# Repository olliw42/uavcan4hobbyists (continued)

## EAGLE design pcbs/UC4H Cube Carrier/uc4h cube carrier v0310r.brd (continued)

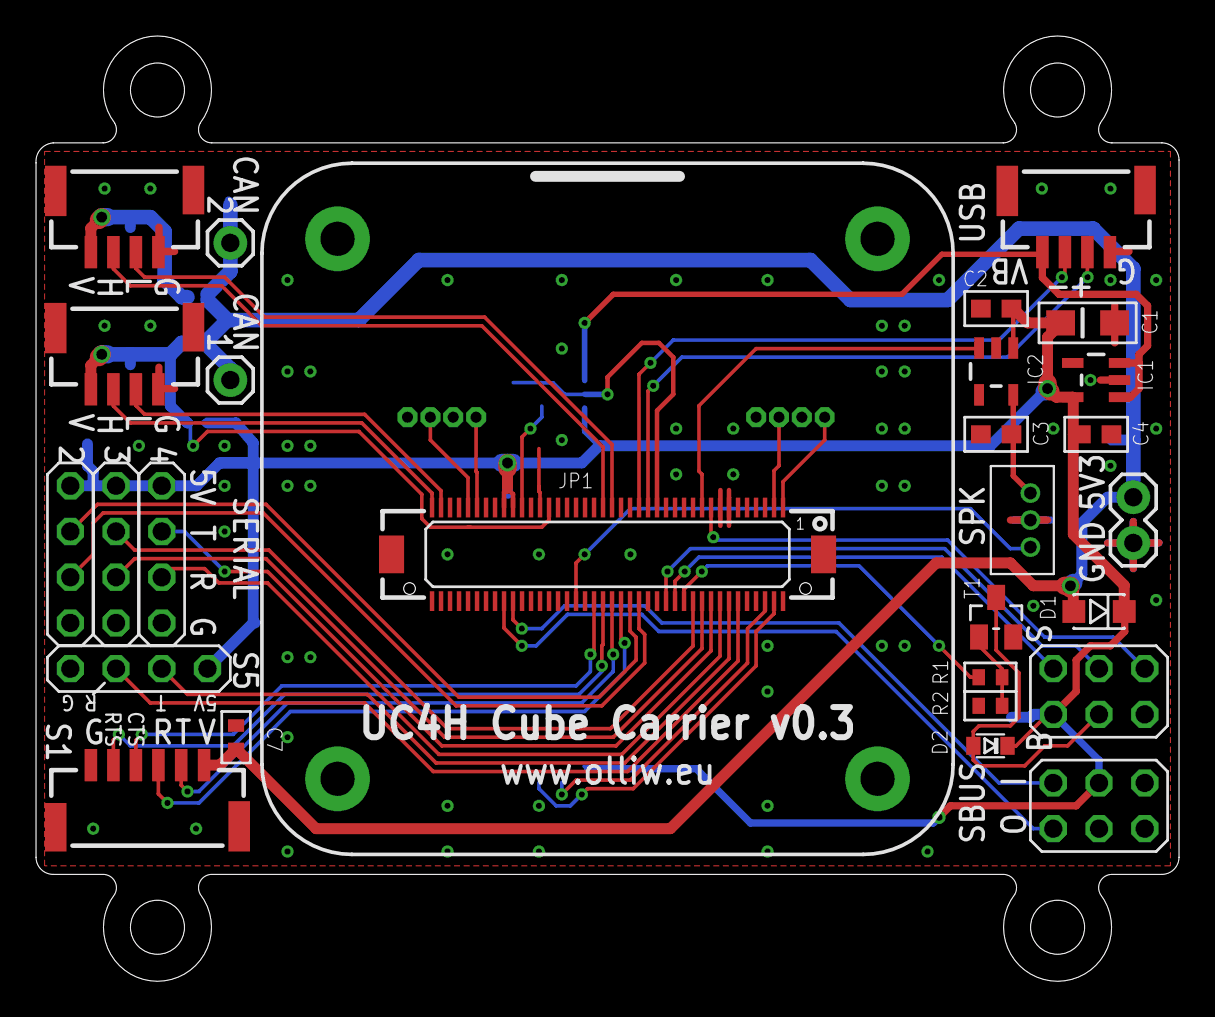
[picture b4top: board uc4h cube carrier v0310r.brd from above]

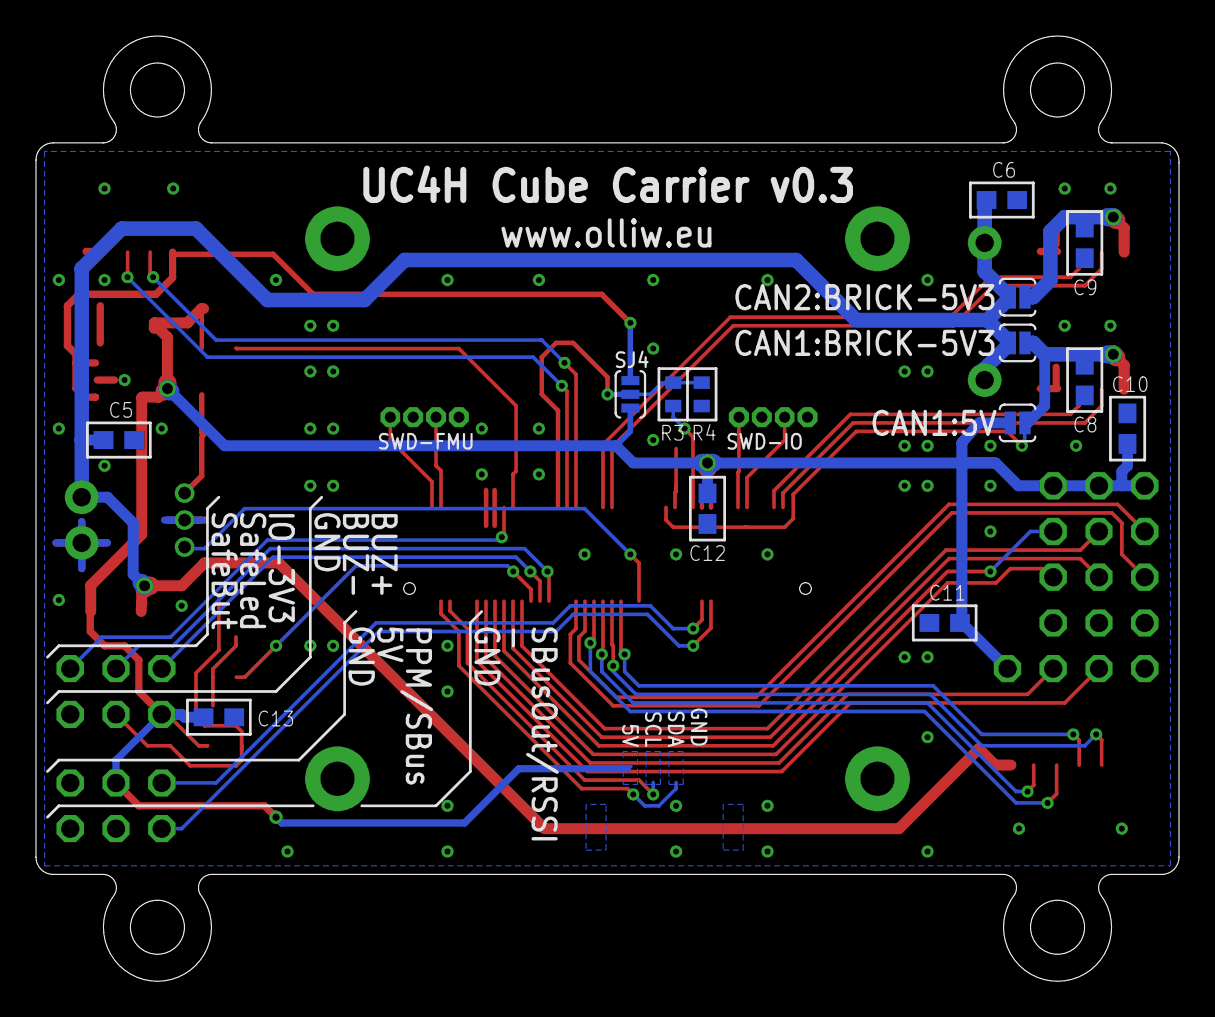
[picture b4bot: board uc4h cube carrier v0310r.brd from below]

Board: 2 copper layers, 63.5 x 52.5 mm, 46 parts (15 on the bottom side), 44 nets.

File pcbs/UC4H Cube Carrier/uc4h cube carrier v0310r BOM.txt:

Stückliste exportiert aus C:/Users/Olli/Documents/GitHub/uavcan4hobbyists/pcbs/UC4H Cube Carrier/uc4h cube carrier v0310r.sch am 06.04.2019 08:51

Part Value                Device                 Package                           Description                          BOM
C1   10u/10V              CPOL-EUSMCA            SMC_A                             POLARIZED CAPACITOR, European symbol    
C2   100n                 C-EUC0603              C0603                             CAPACITOR, European symbol              
C3   100n                 C-EUC0603              C0603                             CAPACITOR, European symbol              
C4   1u                   C-EUC0603              C0603                             CAPACITOR, European symbol              
C5   100n                 C-EUC0603              C0603                             CAPACITOR, European symbol              
C6   100n                 C-EUC0603              C0603                             CAPACITOR, European symbol              
C7   100n                 C-EUC0402              C0402                             CAPACITOR, European symbol              
C8   100n                 C-EUC0603              C0603                             CAPACITOR, European symbol              
C9   100n                 C-EUC0603              C0603                             CAPACITOR, European symbol              
C10  100n                 C-EUC0603              C0603                             CAPACITOR, European symbol              
C11  100n                 C-EUC0603              C0603                             CAPACITOR, European symbol              
C12  100n                 C-EUC0603              C0603                             CAPACITOR, European symbol              
C13  100n                 C-EUC0603              C0603                             CAPACITOR, European symbol              
D1   PMEG3010ER           DIODE-SCHOTTKYSOD123-W SOD123W-DIODE                                                             
D2   BAT54J               DIODE-SOD110-R         SOD110-R                          DIODE                                   
IC1  MAX40200             V_REG_TPS76433SOT23-5  SOT23-5                           Voltage Regulator                       
IC2  TC1185-3.3VCT713     V_REG_TPS76433SOT23-5  SOT23-5                           Voltage Regulator                       
JP1  DF17(1.0H)-80DP-0.5V PIX-CUBE-VIA           PIX-CUBE-DF17(1.0H)-80DP-0.5V-VIA                                         
JP2  USB                  JST-GH-4TOP-ENTRY      BM04B-GHS-TBT                                                             
JP3  SPK                  B3B-ZR                 B3B-ZR                            JST-ZH Connector                        
JP4  CAN1                 JST-GH-4TOP-ENTRY      BM04B-GHS-TBT                                                             
JP5  CAN2                 JST-GH-4TOP-ENTRY      BM04B-GHS-TBT                                                             
JP6  SERIAL1              JST-GH-6TOP-ENTRY      BM06B-GHS-TBT                                                             
JP7  SERIAL2              PINHEAD_4X1            PINHEAD_4X1                                                               
JP8  SERIAL3              PINHEAD_4X1            PINHEAD_4X1                                                               
JP9  SERIAL4              PINHEAD_4X1            PINHEAD_4X1                                                               
JP10 SERIAL5              PINHEAD_4X1            PINHEAD_4X1                                                               
PH1  VDD-BRICK            M02PTH                 1X02                              Header 2                                
PH2  SBUS                 PINHEAD_3X2            PINHEAD_3X2                                                               
PH3  SAFEBUZ              PINHEAD_3X2            PINHEAD_3X2                                                               
PH4  CAN-HIPWR1           M01PTH                 1X01                              Header 1                                
PH5  CAN-HIPWR2           M01PTH                 1X01                              Header 1                                
PH6  SWD                  P4X1_1P27-OCT_BILEX    4X1_1P27_OCT_BILEX                                                        
PH7  SWD2                 P4X1_1P27-OCT_BILEX    4X1_1P27_OCT_BILEX                                                        
R1   10k                  R-EU_R0402             R0402                             RESISTOR, European symbol               
R2   10k                  R-EU_R0402             R0402                             RESISTOR, European symbol               
R3   10k                  R-EU_R0402             R0402                             RESISTOR, European symbol               
R4   470                  R-EU_R0402             R0402                             RESISTOR, European symbol               
SH1  SHORT-HT5            SHORT-HT5              SHORT_TOP-50                      Short between two nets               no 
SH2  SHORT-HT5            SHORT-HT5              SHORT_TOP-50                      Short between two nets               no 
SH3  SHORT-HT5            SHORT-HT5              SHORT_TOP-50                      Short between two nets               no 
SJ1  PWR                  SJ-2WAY-WPASTECONNECT  SJ-2WAY-BIG-WPASTEC                                                       
SJ2  PWR                  SJ-2WAY-STANDARD       SJ-2WAY-BIG                                                               
SJ3  PWR                  SJ-2WAY-WPASTECONNECT  SJ-2WAY-BIG-WPASTEC                                                       
SJ4  SJ-3WAY-03           SJ-3WAY-03             SJ-3WAY-WPASTEC                                                           
T1   FET-NSOT23           FET-NSOT23             SOT23

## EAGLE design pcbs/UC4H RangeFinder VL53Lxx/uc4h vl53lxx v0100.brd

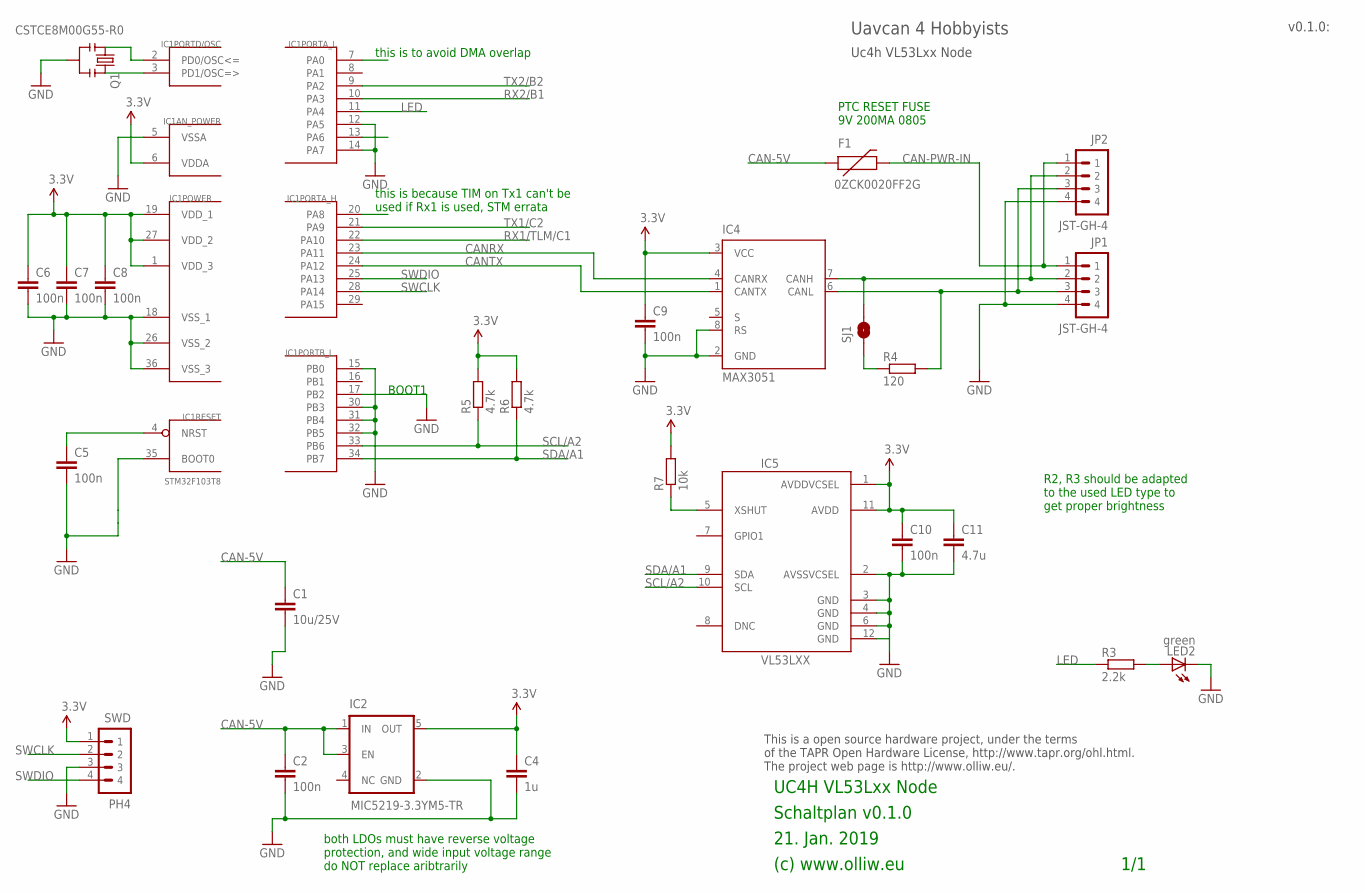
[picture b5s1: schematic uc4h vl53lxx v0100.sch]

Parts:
C1: 10u/25V; C1206
C2: 100n; C0603K
C4: 1u; C0603K
C5, C6, C7, C8, C9, C10: 100n; C0402
C11: 4.7u; C0603K
F1: 0ZCK0020FF2G; FUSE-0805
IC1: STM32F103T8; VFQFPN36
IC2: MIC5219-3.3YM5-TR; SOT23-5
IC4: MAX3051; SOT23-8
IC5: VL53LXX
JP1, JP2: JST-GH-4; SM04B-GHS-TB
LED2: green; CHIPLED_0603
Q1: CSTCE8M00G55-R0; RESONATOR-SMD
R3: 2.2k; R0402
R4: 120; R0402
R5, R6: 4.7k; R0402
R7: 10k; R0402
SJ1: SOLDERJUMPERNO; SJ_2S-NO
SWD: PH4; 4X1_1P27_OCT_BILEX

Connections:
3.3V: C4.1, C6.1, C7.1, C8.1, C9.1, C10.1, C11.1, IC1.1 (VDD_3), IC1.6 (VDDA), IC1.19 (VDD_1), IC1.27 (VDD_2), IC2.5 (OUT), IC4.3 (VCC), IC5.1 (AVDDVCSEL), IC5.11 (AVDD), R5.2, R6.2, R7.2, SWD.1
CAN-5V: C1.1, C2.1, F1.1, IC2.1 (IN), IC2.3 (EN)
CAN-PWR-IN: F1.2, JP1.1, JP2.1
CANH: IC4.7 (CANH), JP1.2, JP2.2, SJ1.2
CANL: IC4.6 (CANL), JP1.3, JP2.3, R4.2
CANRX: IC1.23 (PA11), IC4.4 (CANRX)
CANTX: IC1.24 (PA12), IC4.1 (CANTX)
GND: C1.2, C2.2, C4.2, C5.2, C6.2, C7.2, C8.2, C9.2, C10.2, C11.2, IC1.5 (VSSA), IC1.12 (PA5), IC1.14 (PA7), IC1.15 (PB0), IC1.17 (PB2), IC1.18 (VSS_1), IC1.26 (VSS_2), IC1.30 (PB3), IC1.31 (PB4), IC1.32 (PB5), IC1.35 (BOOT0), IC1.36 (VSS_3), IC2.2 (GND), IC4.2 (GND), IC4.8 (RS), IC5.2 (AVSSVCSEL), IC5.3 (GND), IC5.4 (GND), IC5.6 (GND), IC5.12 (GND), JP1.4, JP2.4, LED2.C, Q1.2, SWD.3
LED: IC1.11 (PA4), R3.1
unnamed: C5.1, IC1.4 (NRST)
unnamed: LED2.A, R3.2
unnamed: R4.1, SJ1.1
unnamed: IC1.2 (PD0/OSC<=), Q1.1
unnamed: IC1.3 (PD1/OSC=>), Q1.3
unnamed: IC5.5 (XSHUT), R7.1
RX1/TLM/C1: IC1.22 (PA10)
RX2/B1: IC1.10 (PA3)
SCL/A2: IC1.33 (PB6), IC5.10 (SCL), R5.1
SDA/A1: IC1.34 (PB7), IC5.9 (SDA), R6.1
SWCLK: IC1.28 (PA14), SWD.2
SWDIO: IC1.25 (PA13), SWD.4
TX1/C2: IC1.21 (PA9)
TX2/B2: IC1.9 (PA2)

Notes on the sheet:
21. Jan. 2019
(c) www.olliw.eu
UC4H VL53Lxx Node
Schaltplan v0.1.0
This is a open source hardware project, under the terms of the TAPR Open Hardware License, http://www.tapr.org/ohl.html. The project web page is http://www.olliw.eu/.
1/1
Uc4h VL53Lxx Node
Uavcan 4 Hobbyists
BOOT1
PTC RESET FUSE 9V 200MA 0805
both LDOs must have reverse voltage protection, and wide input voltage range do NOT replace aribtrarily
this is to avoid DMA overlap
this is because TIM on Tx1 can't be used if Rx1 is used, STM errata
v0.1.0:
R2, R3 should be adapted to the used LED type to get proper brightness

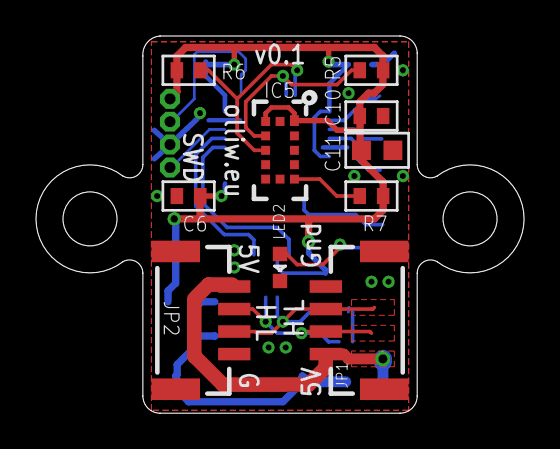
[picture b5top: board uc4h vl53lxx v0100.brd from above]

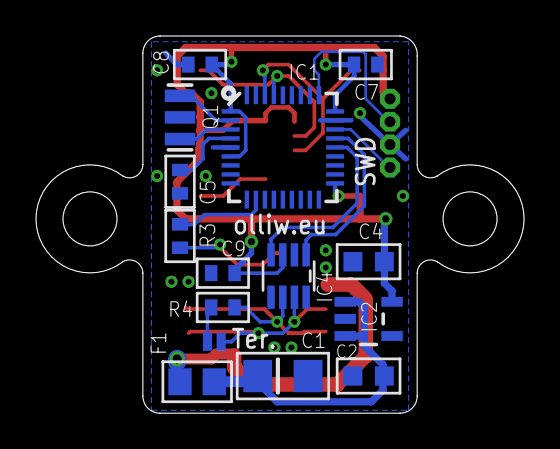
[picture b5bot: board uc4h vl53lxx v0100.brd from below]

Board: 2 copper layers, 27.1 x 21.0 mm, 26 parts (15 on the bottom side), 19 nets.

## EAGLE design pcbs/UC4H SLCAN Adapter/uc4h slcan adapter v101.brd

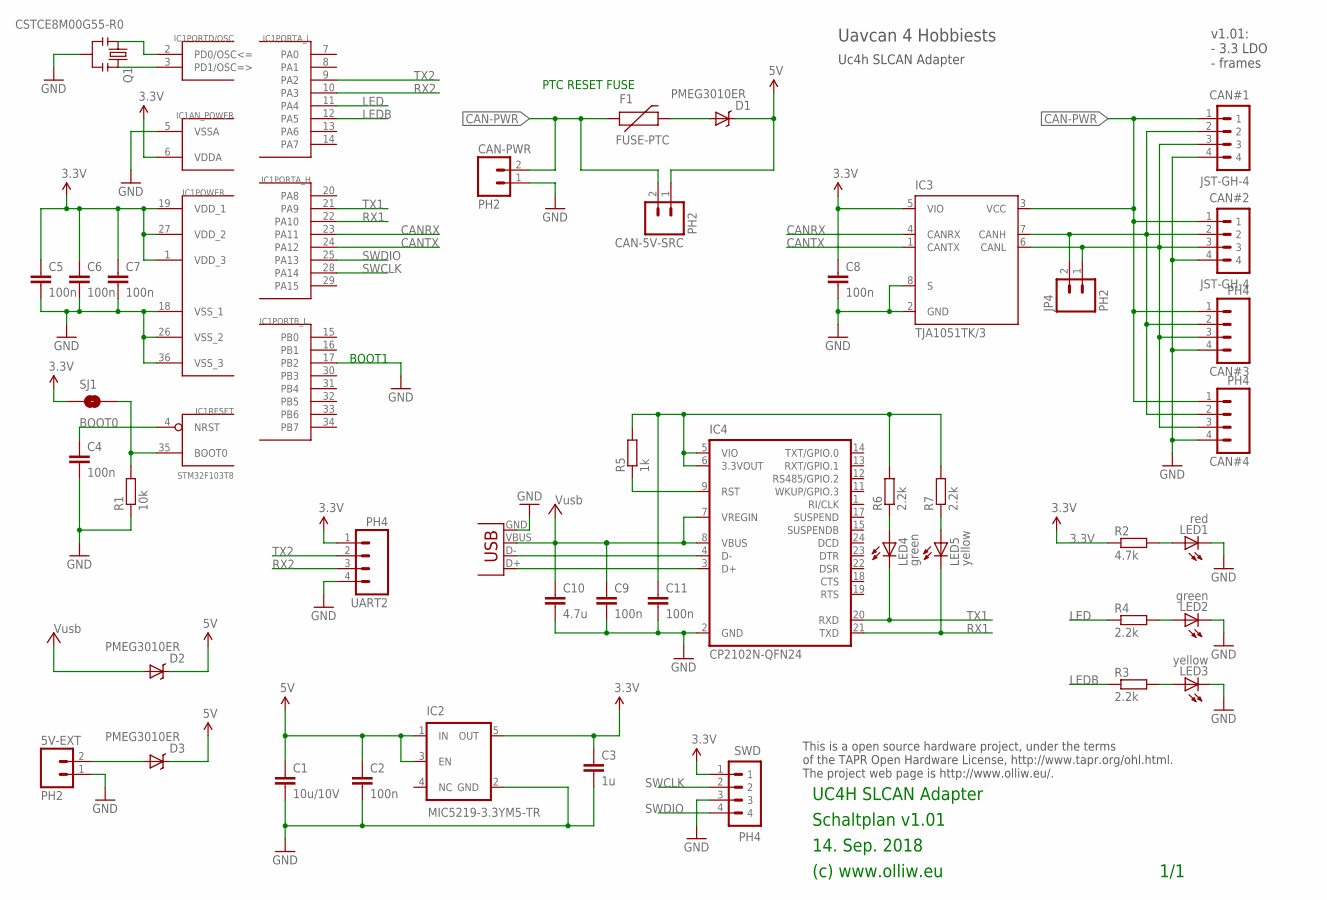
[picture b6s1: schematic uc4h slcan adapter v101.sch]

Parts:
5V-EXT: PH2; 1X02
C1: 10u/10V; C1206
C2, C4, C5, C6, C7, C8, C9, C11: 100n; C0603K
C3: 1u; C0603K
C10: 4.7u; C0805
CAN#1, CAN#2: JST-GH-4; SM04B-GHS-TB
CAN#3, CAN#4: PH4; 1X04
CAN-5V-SRC: PH2; 1X02
CAN-PWR: PH2; 1X02
D1, D2, D3: PMEG3010ER; SOD123W-DIODE
F1: FUSE-PTC; FUSE-1206
IC1: STM32F103T8; VFQFPN36
IC2: MIC5219-3.3YM5-TR; SOT23-5
IC3: TJA1051TK/3; HVSON8
IC4: CP2102N-QFN24; QFN24-CP2102N
JP4: PH2; 1X02
LED1: red; CHIPLED_0603
LED2, LED4: green; CHIPLED_0603
LED3, LED5: yellow; CHIPLED_0603
Q1: CSTCE8M00G55-R0; RESONATOR-SMD
R1: 10k; R0603
R2: 4.7k; R0603
R3, R4, R6, R7: 2.2k; R0603
R5: 1k; R0603
SJ1: BOOT0; SJ_2S-NO
SWD: PH4; 4X1_1P27_OCT_BILEX
UART2: PH4; 1X04
USB: Amphenol 10118192-0001LF; USB-MICROB

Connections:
3.3V: C3.1, C5.1, C6.1, C7.1, C8.1, IC1.1 (VDD_3), IC1.6 (VDDA), IC1.19 (VDD_1), IC1.27 (VDD_2), IC2.5 (OUT), IC3.5 (VIO), R2.1, SJ1.1, SWD.1, UART2.1
3.3V-CP2102: C11.1, IC4.5 (VIO), IC4.6 (3.3VOUT), R5.2, R6.2, R7.2
5V: C1.1, C2.1, CAN-5V-SRC.1, D1.C, D2.C, D3.C, IC2.1 (IN), IC2.3 (EN)
5V-CAN-FUSE: D1.A, F1.4 (2)
CAN-PWR: CAN#1.1, CAN#2.1, CAN#3.1, CAN#4.1, CAN-5V-SRC.2, CAN-PWR.2, F1.3 (1), IC3.3 (VCC)
CANH: CAN#1.2, CAN#2.2, CAN#3.2, CAN#4.2, IC3.7 (CANH), JP4.2
CANL: CAN#1.3, CAN#2.3, CAN#3.3, CAN#4.3, IC3.6 (CANL), JP4.1
CANRX: IC1.23 (PA11), IC3.4 (CANRX)
CANTX: IC1.24 (PA12), IC3.1 (CANTX)
GND: 5V-EXT.1, C1.2, C2.2, C3.2, C4.2, C5.2, C6.2, C7.2, C8.2, C9.2, C10.2, C11.2, CAN#1.4, CAN#2.4, CAN#3.4, CAN#4.4, CAN-PWR.1, IC1.5 (VSSA), IC1.17 (PB2), IC1.18 (VSS_1), IC1.26 (VSS_2), IC1.36 (VSS_3), IC2.2 (GND), IC3.2 (GND), IC3.8 (S), IC4.2 (GND), LED1.C, LED2.C, LED3.C, Q1.2, R1.1, SWD.3, UART2.4, USB.GND
LED: IC1.11 (PA4), R4.1
LEDB: IC1.12 (PA5), R3.1
unnamed: C4.1, IC1.4 (NRST)
unnamed: LED3.A, R3.2
unnamed: IC1.35 (BOOT0), R1.2, SJ1.2
unnamed: IC1.2 (PD0/OSC<=), Q1.1
unnamed: IC1.3 (PD1/OSC=>), Q1.3
unnamed: LED2.A, R4.2
unnamed: LED1.A, R2.2
unnamed: 5V-EXT.2, D3.A
unnamed: IC4.9 (RST), R5.1
unnamed: LED4.A, R6.1
unnamed: IC4.4 (D-), USB.D-
unnamed: LED5.A, R7.1
unnamed: IC4.3 (D+), USB.D+
RX1: IC1.22 (PA10), IC4.21 (TXD), LED5.C
RX2: IC1.10 (PA3), UART2.3
SWCLK: IC1.28 (PA14), SWD.2
SWDIO: IC1.25 (PA13), SWD.4
TX1: IC1.21 (PA9), IC4.20 (RXD), LED4.C
TX2: IC1.9 (PA2), UART2.2
VUSB: C9.1, C10.1, D2.A, IC4.7 (VREGIN), IC4.8 (VBUS), USB.VBUS

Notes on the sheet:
14. Sep. 2018
(c) www.olliw.eu
UC4H SLCAN Adapter
Schaltplan v1.01
This is a open source hardware project, under the terms of the TAPR Open Hardware License, http://www.tapr.org/ohl.html. The project web page is http://www.olliw.eu/.
1/1
Uc4h SLCAN Adapter
Uavcan 4 Hobbiests
BOOT1
v1.01: - 3.3 LDO - frames
PTC RESET FUSE

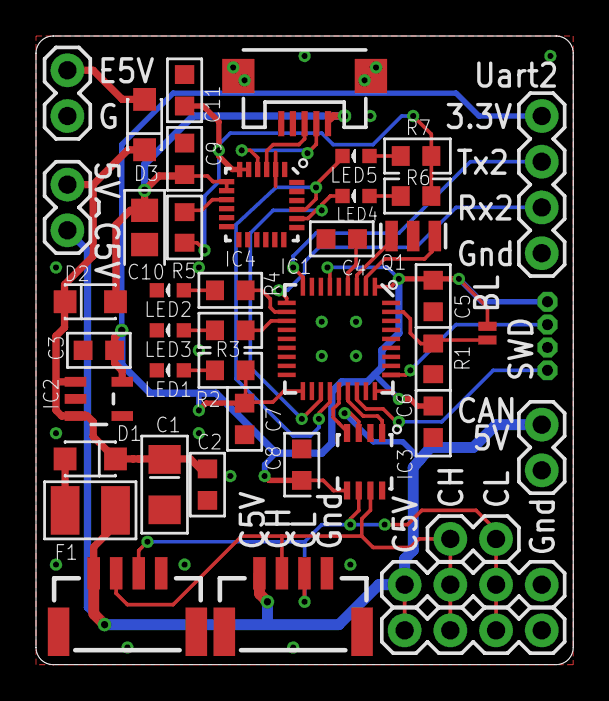
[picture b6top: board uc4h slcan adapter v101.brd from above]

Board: 2 copper layers, 29.8 x 34.9 mm, 44 parts (0 on the bottom side), 32 nets.

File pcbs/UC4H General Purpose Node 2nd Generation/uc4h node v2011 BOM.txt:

Stückliste exportiert aus C:/Users/Olli/Documents/Elektronik/Eagle/Uavcan4Hobby/uc4h node v2010.sch am 02.08.2018 07:51

Part Value             Device                Package            Description                  
C1   10u/25V           C-EUC1206             C1206              CAPACITOR, European symbol   
C2   100n              C-EUC0603K            C0603K             CAPACITOR, European symbol   
C3   1u                C-EUC0603K            C0603K             CAPACITOR, European symbol   
C4   1u                C-EUC0603K            C0603K             CAPACITOR, European symbol   
C5   100n              C-EUC0603K            C0603K             CAPACITOR, European symbol   
C6   100n              C-EUC0603K            C0603K             CAPACITOR, European symbol   
C7   100n              C-EUC0603K            C0603K             CAPACITOR, European symbol   
C8   100n              C-EUC0603K            C0603K             CAPACITOR, European symbol   
C9   100n              C-EUC0603K            C0603K             CAPACITOR, European symbol   
F1   0ZCK0020FF2G      FUSE-PTCFUSE-0805     FUSE-0805                                       
IC1  STM32F103T8       STM32F10XTXU6         VFQFPN36           STM32F101/103 36pad VFQPFN36 
IC2  MIC5219-5.0YM5-TR V_REG_TPS76433SOT23-5 SOT23-5            Voltage Regulator            
IC3  MIC5219-3.3YM5-TR V_REG_TPS76433SOT23-5 SOT23-5            Voltage Regulator            
IC4  TJA1051TK/3       TJA1051TK/3           HVSON8                                          
JP1  JST-GH-4          JST-GH-4              SM04B-GHS-TB                                    
JP2  JST-GH-4          JST-GH-4              SM04B-GHS-TB                                    
JP3                    M04PTH                1X04               Header 4                     
JP5                    M02PTH                1X02               Header 2                     
JP6  M01PTH            M01PTH                1X01               Header 1                     
LED1 red               LEDCHIPLED_0603       CHIPLED_0603       LED                          
LED2 green             LEDCHIPLED_0603       CHIPLED_0603       LED                          
Q1   CSTCE8M00G55-R0   RESONATORSMD          RESONATOR-SMD      Resonator                    
R1   10k               R-EU_R0603            R0603              RESISTOR, European symbol    
R2   4.7k              R-EU_R0603            R0603              RESISTOR, European symbol    
R3   2.2k              R-EU_R0603            R0603              RESISTOR, European symbol    
R4   120               R-EU_R0603            R0603              RESISTOR, European symbol    
R5   10k               R-EU_R0603            R0603              RESISTOR, European symbol    
R6   10k               R-EU_R0603            R0603              RESISTOR, European symbol    
SJ1  BOOT0             SOLDERJUMPERNO        SJ_2S-NO           Solder Jumper                
SJ2                    SOLDERJUMPERNO        SJ_2S-NO           Solder Jumper                
SJ3                    SOLDERJUMPERNO        SJ_2S-NO           Solder Jumper                
SWD  PH4               P4X1_1P27-OCT_BILEX   4X1_1P27_OCT_BILEX

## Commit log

2017-08-08 release v019
2017-11-16 release uc4h esc actuator node v002
2017-11-17 release uc4h esc actuator node v003
2017-11-30 release v021
2018-01-14 esc-actuator v004
2018-02-06 release esc actuator v006
2018-02-09 release uc4h esc v008
2018-02-10 release gps-mag v022, more reliable mag startup
2018-02-18 release uc4h esc v009 and uc4h notify v002
2018-02-21 release UC4H ESC KISS and Mini Eagle layouts
2018-02-21 terms of usage
2018-02-21 readme bump
2018-02-23 group order stuff added
2018-02-25 release esc v0.10 notify v0.03
2018-02-27 esc thrust curve .py
2018-02-28 esc thr curve script improved
2018-02-28 esc thr curve script updated
2018-03-03 uc4h esc setup py script v001
2018-03-26 release uc4h-esc v011 and esc_setup v002
2018-03-31 release bootloader-v003, updated esc v012, notify v004
2018-03-31 release uc4h-esc v013
2018-04-04 release uc4h-esc v014
2018-04-04 some clean up
2018-04-04 add firmware readme
2018-04-04 firmware readme
2018-07-09 release airspeed v004 firmwares
2018-07-15 release uartbridge v002 firmwares
2018-07-15 readme
2018-07-19 release uartbridge v003 firmware
2018-07-22 release gps-mag v023 firmware
2018-07-22 release uartbridge v004 firmware
2018-08-02 release firmware notifydisplay v0.07
2018-08-02 release firmware oreoled v0.04
2018-08-02 release board uc4h node v2.0.10
2018-08-10 release airspeed v005 firmwares
2018-08-14 release airspeed v006 firmware
2018-08-17 release board uc4h air/airspeed v0.2.0
2018-08-17 readme update
2018-08-17 release esc actuator v016 firmware
2018-09-14 release UC4H SLCAN adapter v1.01 layout
2018-09-14 release board UC4H Node v2.0.11
2018-09-18 release fun thing v0.01 firmware
2018-09-22 release firmware funthing v002
2018-09-22 release firmware funthing v003
2018-09-27 release board UC4H Node v2.1.00
2018-09-27 release slcan v008 firmware
2018-09-28 release firmware funthing v004
2018-09-28 uavcan dsdl files uavcan.olliw
2018-09-29 release firmware funthing v005
    dynamic node id allocation added
2018-09-29 release firmware funthing v005
2018-09-29 release firmware esc-actuator v017
2018-09-29 release firmware funthing v005
    dynamic node allocation, setup shortname
2018-09-29 release firmware airspeed v007
    dynamic node allocation, setup shortname
2018-09-29 release firmware uartbridge v005
    dynamic node allocation, setup shortname
2018-09-29 release firmware esc-actuator v017
    dynamic node id allocation, setup shortname
2018-10-02 dsdl files updated, include .hpp and .uavcan
2018-10-02 snapshot of binaries compatible with betacopter36dev-v011/v010/v009
2018-10-02 cleanup, bootloader v004, slcan v008
2018-10-02 some rearrangments
2018-10-02 cleanups
2018-10-02 parameter screenshots
2018-10-03 release firmwares all nodes
2018-10-04 release bootloader v005
2018-10-29 uc4h gps mag baro parameter screenshoots
2018-11-01 release new parameter screenshots
2018-11-01 release olliw's parameters
2018-11-10 release uc4 escactuator firmware v0.20
    bug in temperature, wasn't converted for C to K
2018-11-10 release betacopter 3.6.1 v0.14u
2018-11-15 release betacopter 3.6.1 v0.15u
2018-11-22 release uc4h-escactuator v0.21 firmware
2018-12-02 release firmware esc-actuator v0.22
2018-12-03 README updates
2018-12-03 param screenshoots updated
2018-12-08 UC4H Airpseed v0.401 pcb released
2019-01-13 release mavlinkbridge v006, gpsmagbaro v027, powerbrick v010, betacopter v017u
2019-01-13 release powerbrick v010
2019-01-19 Parameter file for MissionPlanner updated
2019-01-20 release uc4h notify firmware v010
    adds a 70ms delay at startup, thx to ppoirier for help
2019-02-15 release RangeFinder v0.03, GpsMagBaro v0.28, UartBridge v0.08, Bootloader v0.07, BetaCopter 3.6.6-v018u
2019-02-15 release PCB UC4H RangeFinder TFMini Carrier
2019-02-24 release PCB UC4H RangeFinder VL53Lxx v0.1.00
2019-02-24 betacopter 3.6.6 v019u rc1
2019-03-12 release betacopter 3.6.7 v019u
2019-03-13 airspeed v0.12
2019-03-15 v3,v4 removed
2019-03-15 betacopter 3.6.7 v020u released
2019-04-06 release UC4H Cube Carrier v0.3 pcb
2019-04-06 release UC4H GpsMagBaroLed Carrier v0.3 pcb
2019-04-06 move up UC4H Airspeed v0.4 pcb
2019-04-06 release firmware airspeed v0.13
2019-04-06 release firmware powerbrick v0.11
2019-04-06 release firmware notify v0.11
2019-04-09 beta
2020-02-29 release firmware rangefinder v0.05
